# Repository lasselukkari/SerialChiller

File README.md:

# SerialChiller
> ESP32 and MAX3232 based wireless RS232 adapter for the Internet of old things.

## Build video

## Wiring
The wiring is implemented as DTE. RS232 TX and RX are connected to the default Serial2 pins IO16 and IO17. RTS is connected to IO21 and CTS to IO22.

## Partlist
| Part         | Value          | Package      | Part #           |
| ------------ | -------------- | ------------ | ---------------- |
| C1           | 0.1uF          | C0603        | C0603X104K5RAC   |
| C2           | 0.1uF          | C0603        | C0603X104K5RAC   |
| C3           | 0.1uF          | C0603        | C0603X104K5RAC   |
| C4           | 0.1uF          | C0603        | C0603X104K5RAC   |
| C5           | 0.1uF          | C0603        | C0603X104K5RAC   |
| C6           | 22uf           | A/3216-18R   | T491A226M010AT   |
| C7           | 22uf           | A/3216-18R   | T491A226M010AT   |
| C8           | 22uF           | C1206        | LMK316ABJ226KL-T |
| C9           | 0.1uF          | C0603        | C0603X104K5RAC   |
| C10          | 0.1uF          | C0603        | C0603X104K5RAC   |
| ESP-WROOM-32 | ESP-WROOM-32   | ESP-WROOM-32 | ESP-WROOM-32     |
| IC1          | LM1117IMPX-3.3 | SOT223       | NCV1117ST33T3G   |
| MAX3232      | MAX3232CSE     | SO16         | MAX3232IDR       |
| R1           | 10k            | R0603        | NRC06J103TRF     |
| RS232        | 56F402-001     | 56F402-001   | 56F402-001       |
| S1           | B3U-1000P      | SW_B3U-1000P | B3U-1000P        |
| S2           | B3U-1000P      | SW_B3U-1000P | B3U-1000P        |
| SERIAL       | Serial         | 1X02         | pinhead          |
| VIN          | Power          | 1X02         | pinhead          |

## PCB Thickness
Use 0.8mm thick pcb to make the board align horisontally with the case.

## Other components
### Case

The plastic housing is taken from a cheap vga break out board available from multiple different vendors. Search eBay or Aliexpress for `DB15 breakout`. 

### USB to TTL Cable

USB to TTL serial adapter cable for powering and flashing the board.

### Strain Relief

Print the strain_relief.stl out of any plastic material to properly secure the cable to the housing.

### Cord Sleeve

The black 4mm cord sleeve is available from multiple different vendors. Snip the end off to make it fit. Search eBay or Aliexpress for `4mm cord sleeve` or `4mm strain relief`.

## Installation
Make sure that the thumb screws are properly tightened or remove them completely. A loose thumb screw may short circuit the electronics.

When used with an extension cable the thumb screws can be replaced with #4-40 jackscrews.

## Power Supply
Any standard usb charger will work fine. The average power consumption is under 500mA.

## Example projects
https://github.com/lasselukkari/DuinoDCX

https://github.com/AlphaLima/ESP32-Serial-Bridge

## License
Creative Commons — Attribution 4.0 International

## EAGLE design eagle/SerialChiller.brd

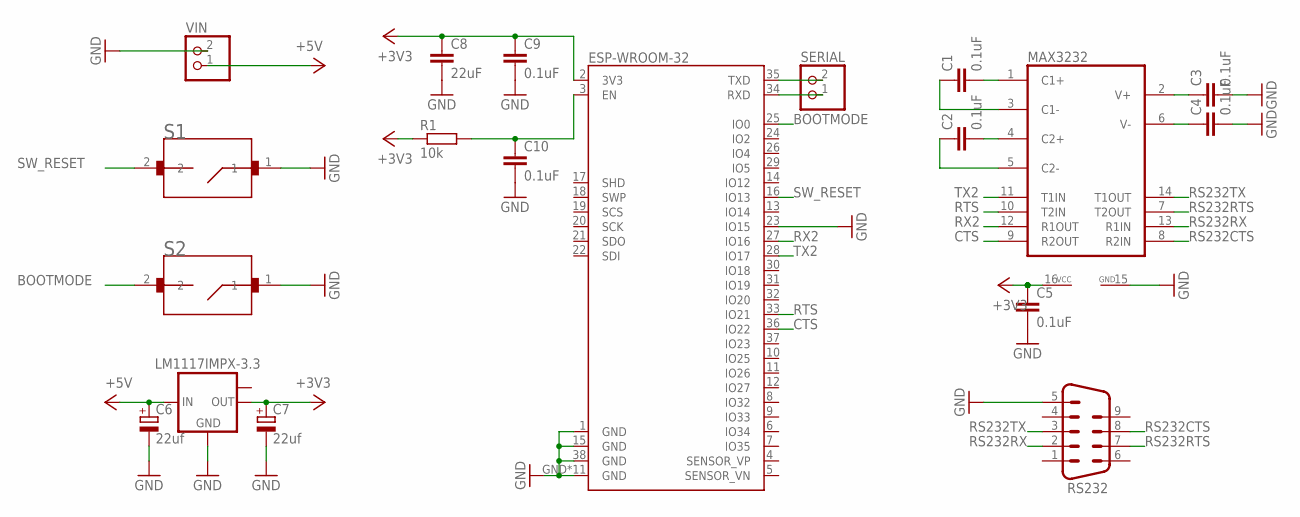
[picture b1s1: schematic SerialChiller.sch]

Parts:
C1, C2, C3, C4, C5, C9, C10: 0.1uF; C0603
C6, C7: 22uf; A/3216-18R
C8: 22uF; C1206
ESP-WROOM-32: ESP-WROOM-03
IC1: LM1117IMPX-3.3; SOT223
MAX3232: MAX3232CSE; SO16
R1: 10k; R0603
RS232: M09HP
S1, S2: B3U-1000P; SW_B3U-1000P
SERIAL: Serial; 1X02
VIN: Power; 1X02

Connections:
+3V3: C5.1, C7.+, C8.1, C9.1, ESP-WROOM-32.2 (3V3), IC1.2 (OUT), MAX3232.16 (VCC), R1.1
+5V: C6.+, IC1.3 (IN), VIN.1
BOOTMODE: ESP-WROOM-32.25 (IO0), S2.2
C1+: C1.2, MAX3232.1 (C1+)
C1-: C1.1, MAX3232.3 (C1-)
C2+: C2.2, MAX3232.4 (C2+)
C2-: C2.1, MAX3232.5 (C2-)
CTS: ESP-WROOM-32.36 (IO22), MAX3232.9 (R2OUT)
ENABLE: C10.1, ESP-WROOM-32.3 (EN), R1.2
GND: C3.2, C4.2, C5.2, C6.-, C7.-, C8.2, C9.2, C10.2, ESP-WROOM-32.1 (GND), ESP-WROOM-32.15 (GND), ESP-WROOM-32.23 (IO15), ESP-WROOM-32.38 (GND), ESP-WROOM-32.GND, ESP-WROOM-32.GND1 (GND), ESP-WROOM-32.P$1 (GND), ESP-WROOM-32.P$2 (GND), ESP-WROOM-32.P$3 (GND), ESP-WROOM-32.P$4 (GND), ESP-WROOM-32.P$5 (GND), ESP-WROOM-32.P$6 (GND), ESP-WROOM-32.P$7 (GND), ESP-WROOM-32.P$8 (GND), ESP-WROOM-32.P$9 (GND), IC1.1 (GND), MAX3232.15 (GND), RS232.5, S1.1, S2.1, VIN.2
RS232CTS: MAX3232.8 (R2IN), RS232.8
RS232RTS: MAX3232.7 (T2OUT), RS232.7
RS232RX: MAX3232.13 (R1IN), RS232.2
RS232TX: MAX3232.14 (T1OUT), RS232.3
RTS: ESP-WROOM-32.33 (IO21), MAX3232.10 (T2IN)
RX1: ESP-WROOM-32.34 (RXD), SERIAL.1
RX2: ESP-WROOM-32.27 (IO16), MAX3232.12 (R1OUT)
SW_RESET: ESP-WROOM-32.16 (IO13), S1.2
TX1: ESP-WROOM-32.35 (TXD), SERIAL.2
TX2: ESP-WROOM-32.28 (IO17), MAX3232.11 (T1IN)
VS+: C3.1, MAX3232.2 (V+)
VS-: C4.1, MAX3232.6 (V-)

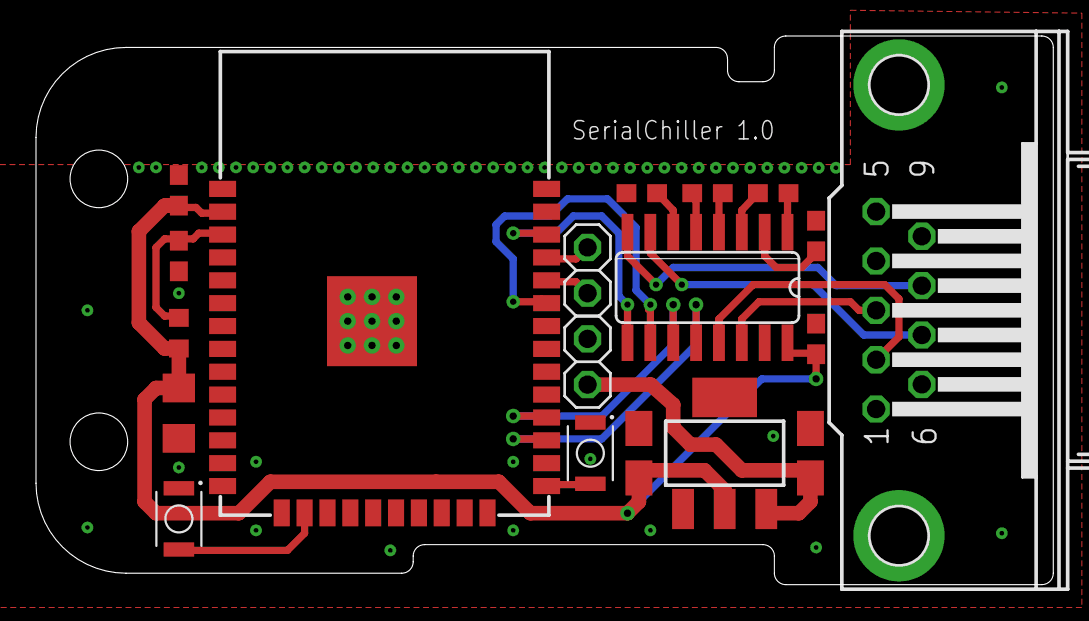
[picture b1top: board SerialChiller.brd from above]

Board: 2 copper layers, 56.5 x 30.5 mm, 19 parts (0 on the bottom side), 22 nets.

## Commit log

2018-10-21 Add content
2018-10-21 Add license
2018-11-22 Remove gerbers
2019-01-31 Add build video
